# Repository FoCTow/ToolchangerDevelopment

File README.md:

# ToolchangerDevelopment
Overengineered 3D Printer Design

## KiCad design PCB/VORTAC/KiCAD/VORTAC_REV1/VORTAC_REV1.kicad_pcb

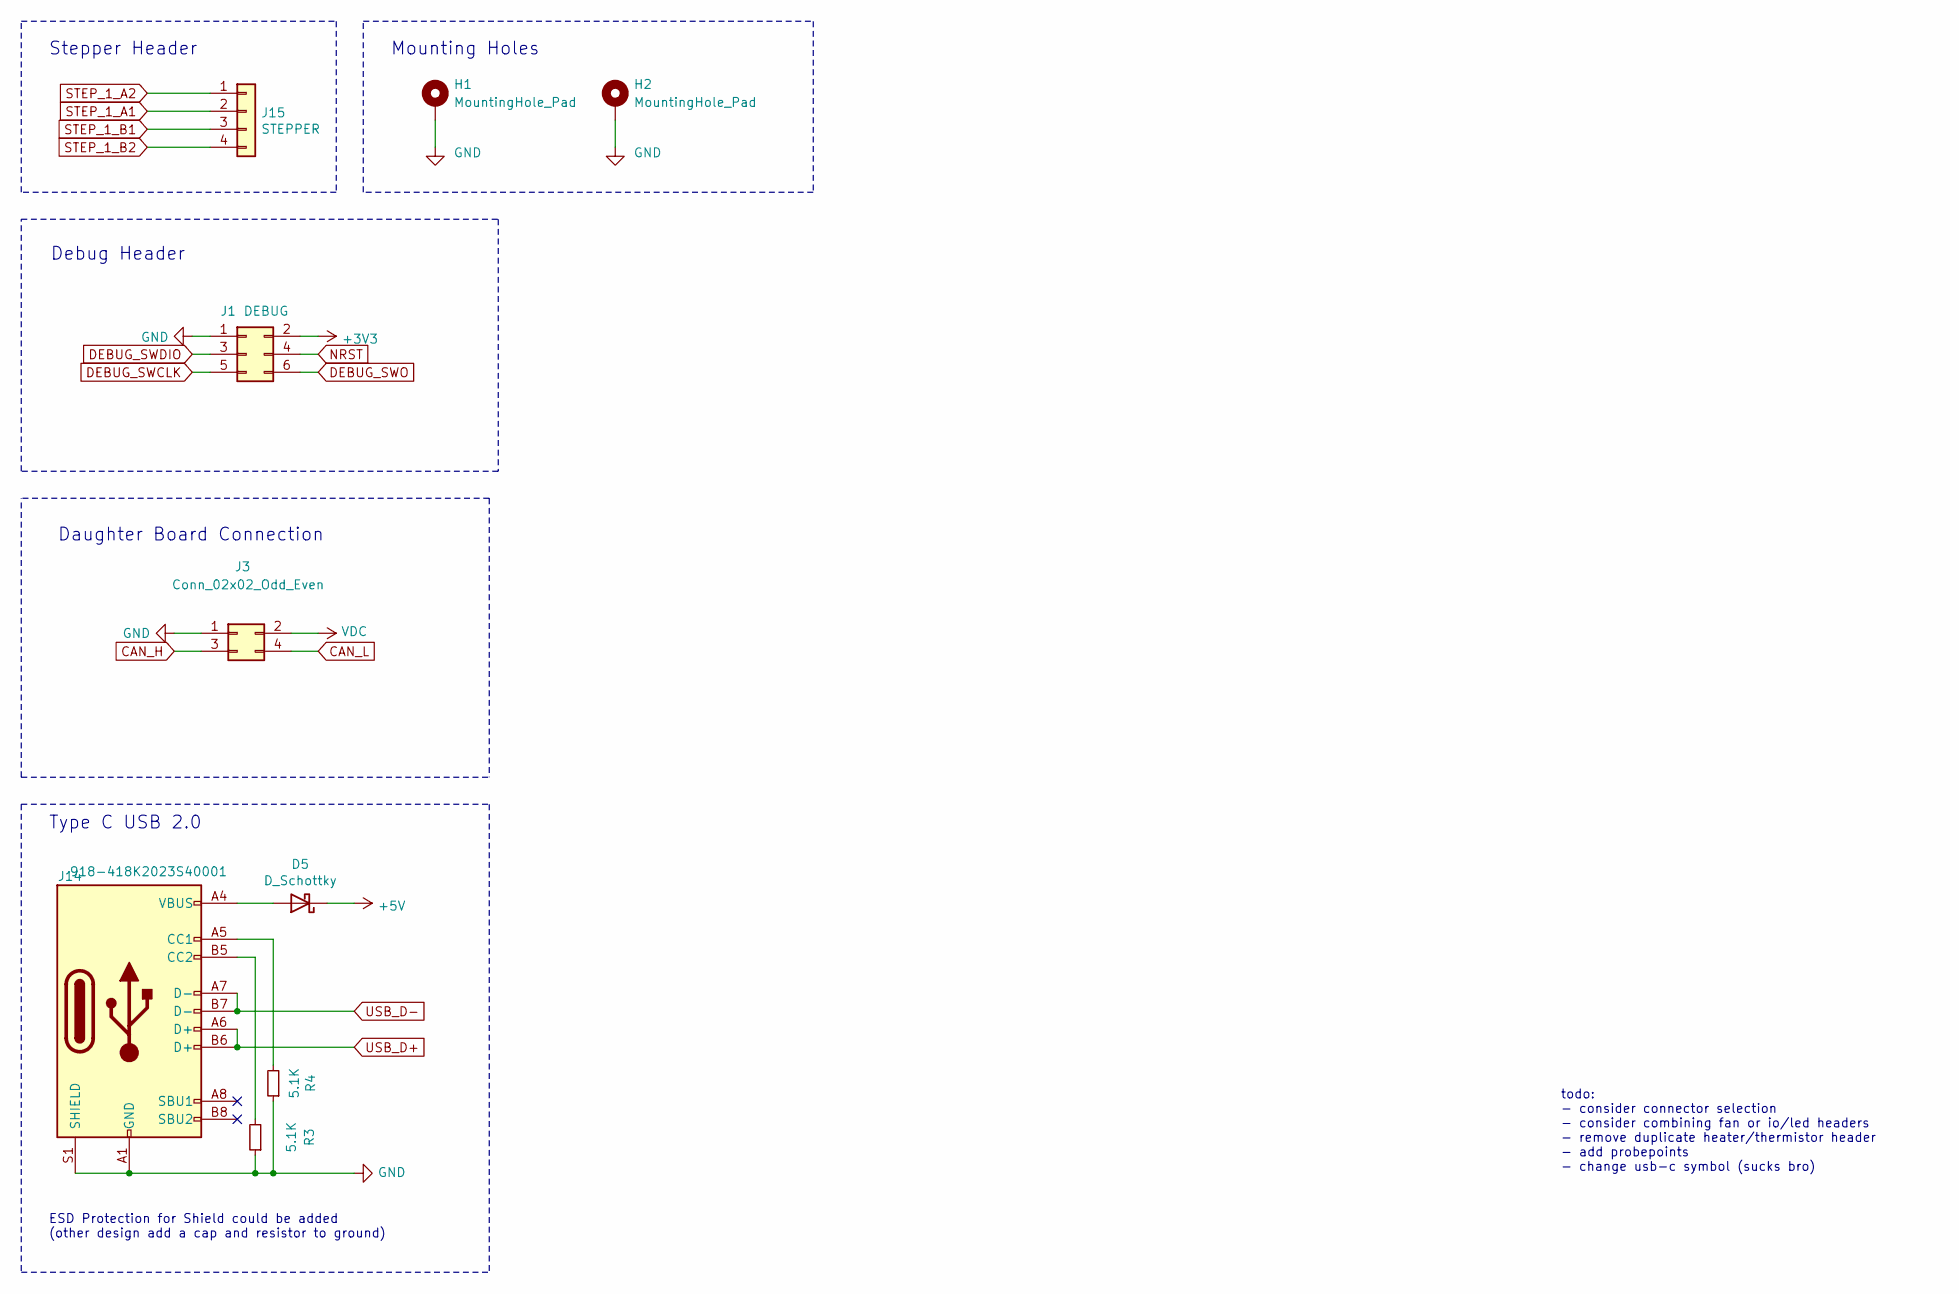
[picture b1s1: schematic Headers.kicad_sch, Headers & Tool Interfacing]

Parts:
D5: D_Schottky; D_SOD-323; LCSC C7420331
H1, H2: MountingHole_Pad; MountingHole_2.2mm_M2_Pad_Via_NTR
J1: DEBUG; PinSocket_2x03_P2.54mm_Vertical; LCSC C541853
J3: Conn_02x02_Odd_Even; PinHeader_2x02_P2.54mm_Vertical; LCSC C7501273
J14: 918-418K2023S40001; USB-C-SMD_TYPEC-303-ACP16; LCSC C720628
J15: STEPPER; Motor_Hand_Wire_pads
R3, R4: 5.1K; R_0402_1005Metric; LCSC C105872

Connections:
+3V3: J1.2; also elsewhere on the board
+5V: D5.1 (K); also elsewhere on the board
CAN_H: J3.3; also elsewhere on the board
CAN_L: J3.4; also elsewhere on the board
DEBUG_SWCLK: J1.5; also elsewhere on the board
DEBUG_SWDIO: J1.3; also elsewhere on the board
DEBUG_SWO: J1.6; also elsewhere on the board
GND: H1.1, H2.1, J1.1, J3.1, J14.A1 (GND), J14.A12 (GND), J14.B1 (GND), J14.B12 (GND), J14.S1 (SHIELD), R3.1, R4.1; also elsewhere on the board
NRST: J1.4; also elsewhere on the board
unnamed: D5.2 (A), J14.A4 (VBUS), J14.A9 (VBUS), J14.B4 (VBUS), J14.B9 (VBUS)
unnamed: J14.A5 (CC1), R4.2
unnamed: J14.B5 (CC2), R3.2
STEP_1_A1: J15.2; also elsewhere on the board
STEP_1_A2: J15.1; also elsewhere on the board
STEP_1_B1: J15.3; also elsewhere on the board
STEP_1_B2: J15.4; also elsewhere on the board
USB_D+: J14.A6 (D+), J14.B6 (D+); also elsewhere on the board
USB_D-: J14.A7 (D-), J14.B7 (D-); also elsewhere on the board
VDC: J3.2; also elsewhere on the board

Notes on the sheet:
todo: - consider connector selection - consider combining fan or io/led headers - remove duplicate heater/thermistor header - add probepoints - change usb-c symbol (sucks bro)
Daughter Board Connection
Stepper Header
Debug Header
Type C USB 2.0
ESD Protection for Shield could be added (other design add a cap and resistor to ground)
Mounting Holes

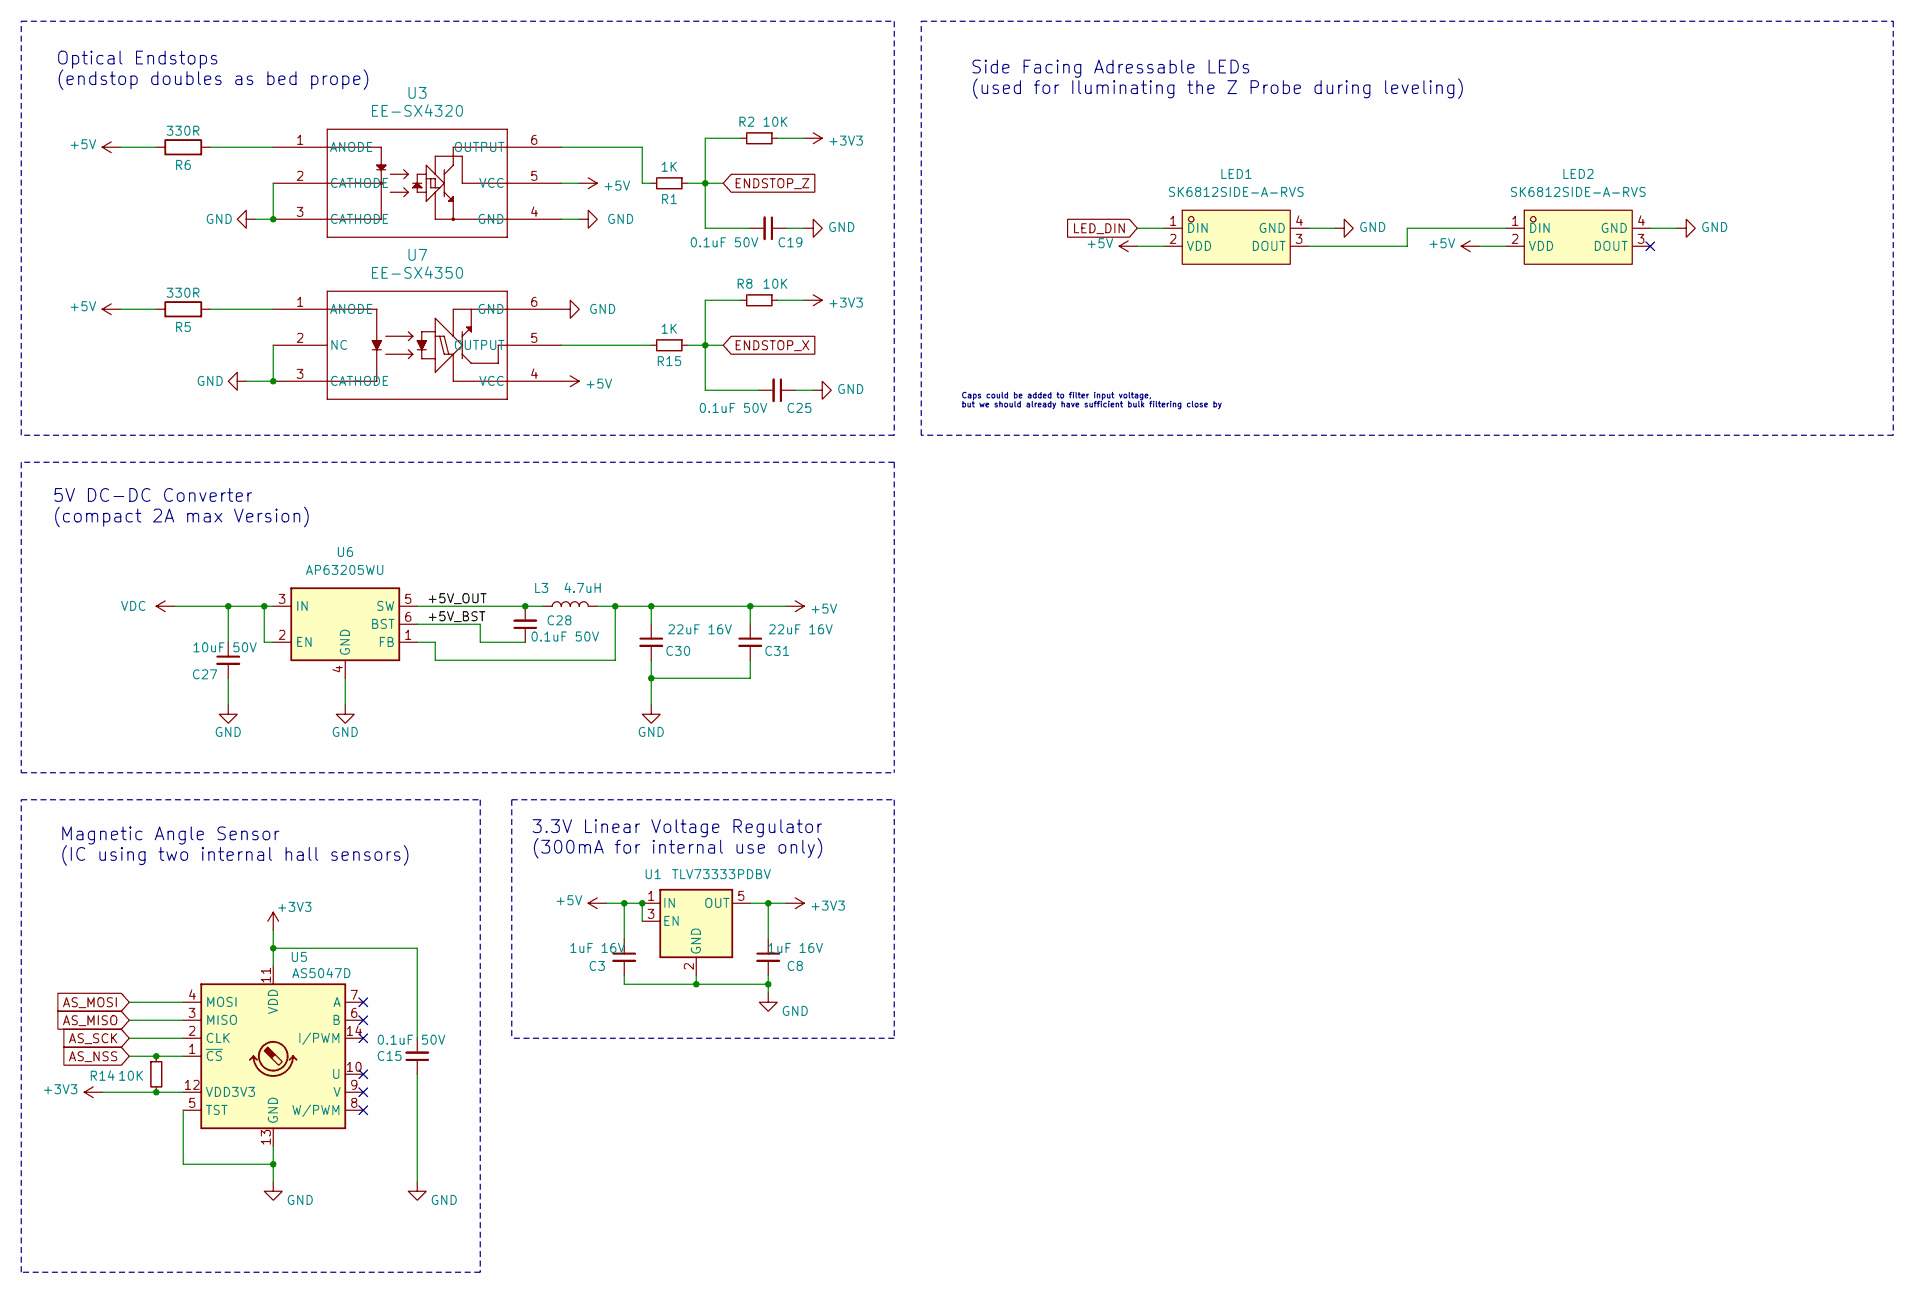
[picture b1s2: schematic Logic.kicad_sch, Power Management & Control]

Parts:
C3, C8: 1uF 16V; C_0603_1608Metric; LCSC C106248
C15, C19, C25, C28: 0.1uF 50V; C_0402_1005Metric; LCSC C5182432
C27: 10uF 50V; C_0805_2012Metric; LCSC C440198
C30, C31: 22uF 16V; C_0603_1608Metric; LCSC C2762594
L3: 4.7uH; IND-SMD_L4.0-W4.0_FNR40XXS; LCSC C167874
LED1, LED2: SK6812SIDE-A-RVS; LED-SMD_4P-L4.0-W1.6-L; LCSC C2890037
R1, R15: 1K; R_0402_1005Metric; LCSC C106235
R2, R8, R14: 10K; R_0402_1005Metric; LCSC C60490
R5, R6: 330R; R_0402_1005Metric; LCSC C6117577
U1: TLV73333PDBV; SOT-23-5; LCSC C408972
U3: EE-SX4320; SENSOR_EE-SX4320_OMR; LCSC C469129
U5: AS5047D; TSSOP-14_4.4x5mm_P0.65mm; LCSC C2693743
U6: AP63205WU; TSOT-23-6; LCSC C2071056
U7: EE-SX4350; SENSOR_EE-SX3350_OMR; LCSC C17524058

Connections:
+3V3: C8.1, C15.2, R2.1, R8.1, R14.2, U1.5 (OUT), U5.11 (VDD), U5.12 (VDD3V3); also elsewhere on the board
+5V: C3.1, C30.1, C31.1, L3.2, LED1.2 (VDD), LED2.2 (VDD), R5.1, R6.1, U1.1 (IN), U1.3 (EN), U3.5 (VCC), U6.1 (FB), U7.4 (VCC); also elsewhere on the board
/Logic/+5V_BST: C28.1, U6.6 (BST)
/Logic/+5V_OUT: C28.2, L3.1, U6.5 (SW)
AS_MISO: U5.3 (MISO); also elsewhere on the board
AS_MOSI: U5.4 (MOSI); also elsewhere on the board
AS_NSS: R14.1, U5.1 (~CS); also elsewhere on the board
AS_SCK: U5.2 (CLK); also elsewhere on the board
ENDSTOP_X: C25.2, R8.2, R15.1; also elsewhere on the board
ENDSTOP_Z: C19.2, R1.1, R2.2; also elsewhere on the board
GND: C3.2, C8.2, C15.1, C19.1, C25.1, C27.2, C30.2, C31.2, LED1.4 (GND), LED2.4 (GND), U1.2 (GND), U3.2 (CATHODE), U3.3 (CATHODE), U3.4 (GND), U5.5 (TST), U5.13 (GND), U6.4 (GND), U7.2 (NC), U7.3 (CATHODE), U7.6 (GND); also elsewhere on the board
LED_DIN: LED1.1 (DIN); also elsewhere on the board
unnamed: LED1.3 (DOUT), LED2.1 (DIN)
unnamed: R6.2, U3.1 (ANODE)
unnamed: R1.2, U3.6 (OUTPUT)
unnamed: R5.2, U7.1 (ANODE)
unnamed: R15.2, U7.5 (OUTPUT)
VDC: C27.1, U6.2 (EN), U6.3 (IN); also elsewhere on the board

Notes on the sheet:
Magnetic Angle Sensor (IC using two internal hall sensors)
Side Facing Adressable LEDs (used for Iluminating the Z Probe during leveling)
Optical Endstops (endstop doubles as bed prope)
3.3V Linear Voltage Regulator (300mA for internal use only)
Caps could be added to filter input voltage, but we should already have sufficient bulk filtering close by
5V DC-DC Converter (compact 2A max Version)

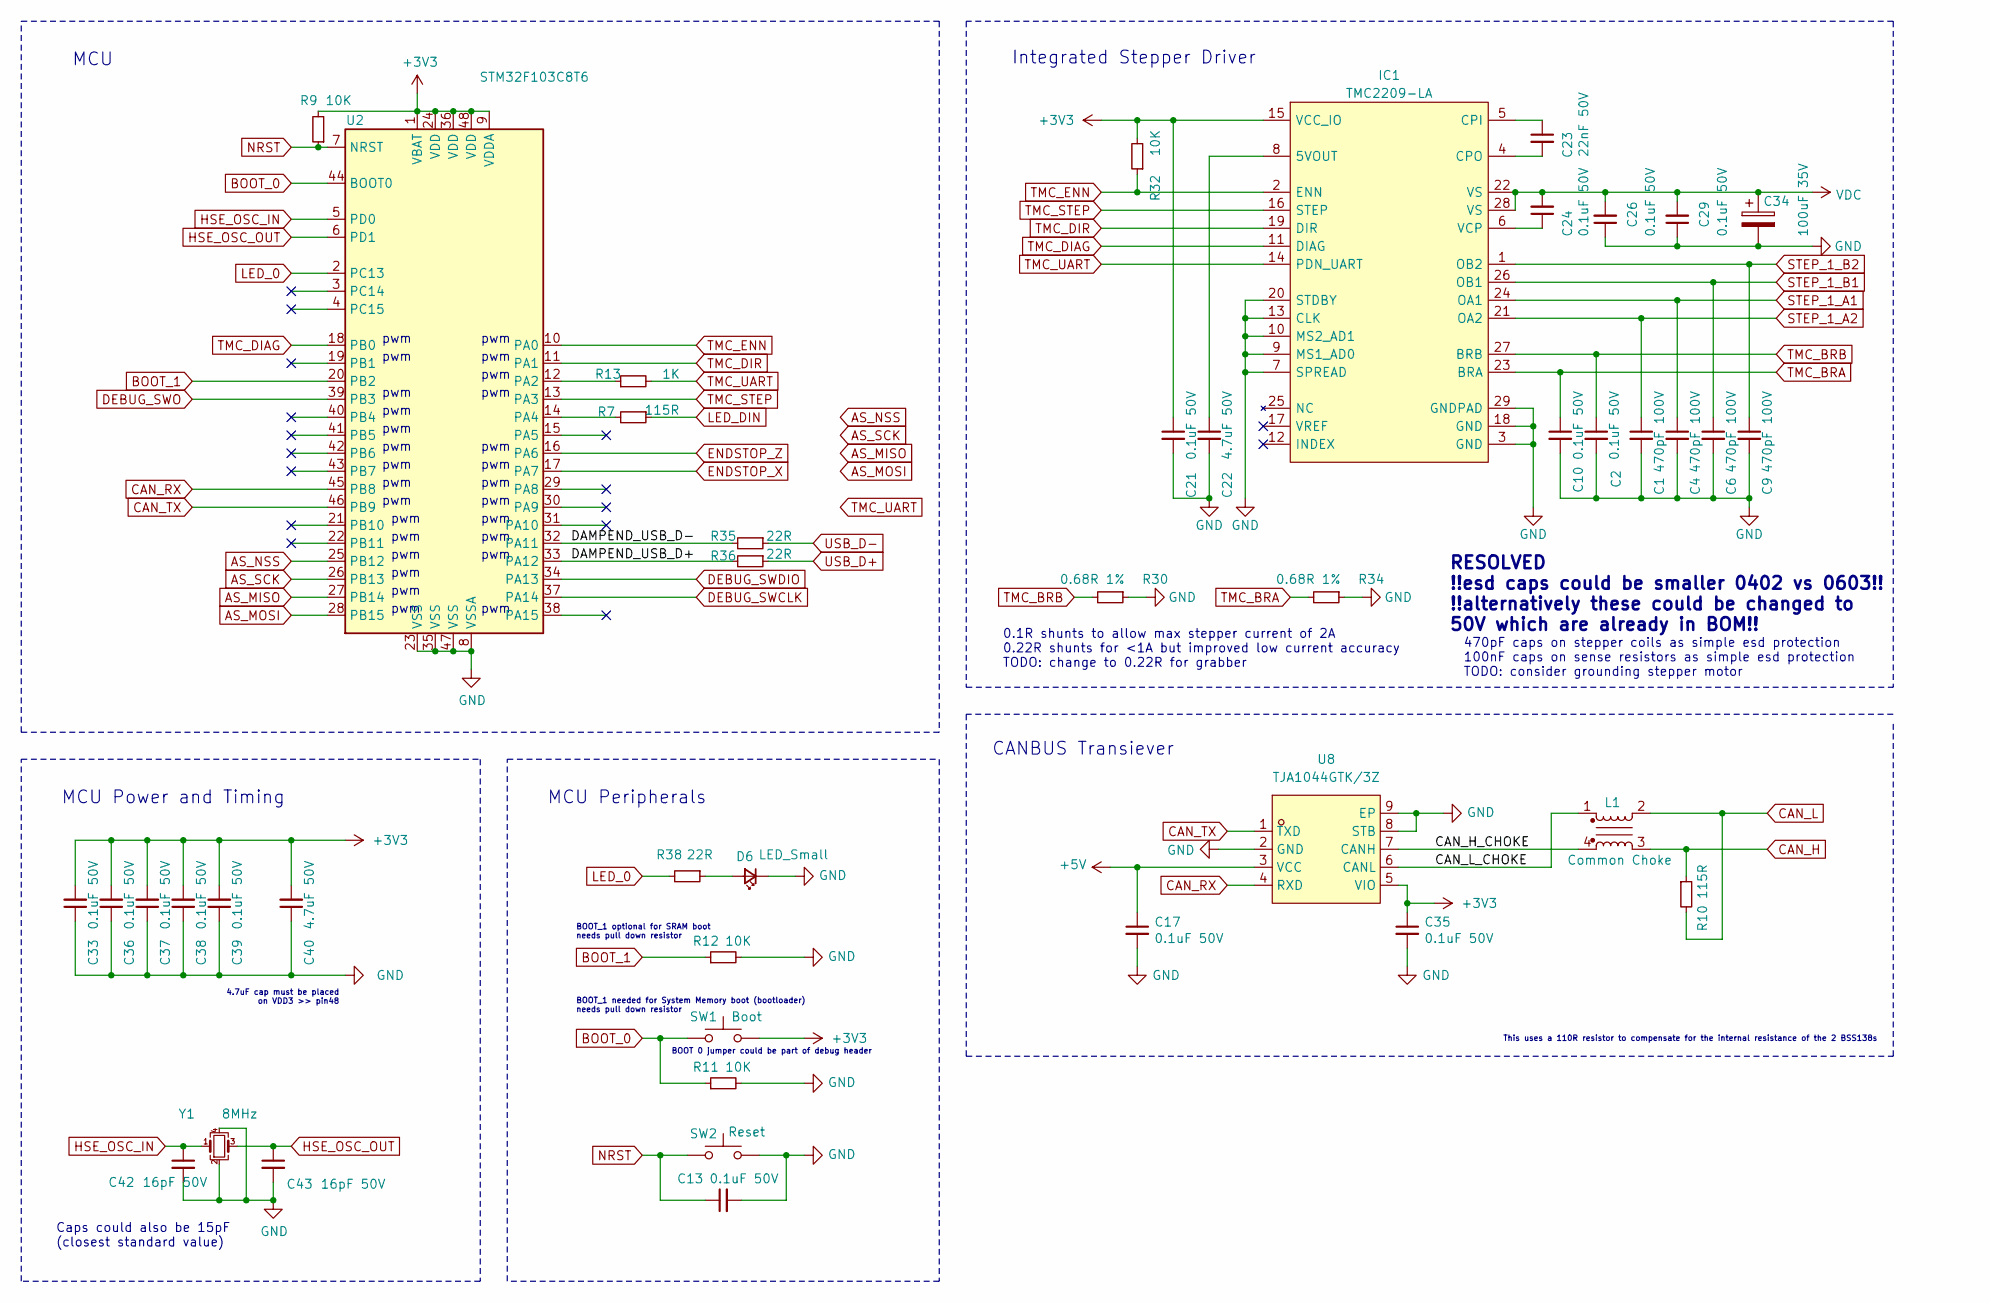
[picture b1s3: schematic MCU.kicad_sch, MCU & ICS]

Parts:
C1, C4, C6, C9: 470pF 100V; C_0603_1608Metric; LCSC C326973
C2, C10, C13, C17, C21, C24, C26, C29, C33, C35, C36, C37, C38, C39: 0.1uF 50V; C_0402_1005Metric; LCSC C5182432
C22, C40: 4.7uF 50V; C_0603_1608Metric; LCSC C513577
C23: 22nF 50V; C_0402_1005Metric; LCSC C107026
C34: 100uF 35V; CP_Elec_6.3x7.7; LCSC C2983388
C42, C43: 16pF 50V; C_0402_1005Metric; LCSC C513591
D6: LED_Small; LED_0402_1005Metric; LCSC C130724
IC1: TMC2209-LA; tmc_2209_package; LCSC C2150710
L1: Common Choke; L_CommonModeChoke_Coilcraft_0805USB; LCSC C3029267
R7, R10: 115R; R_0402_1005Metric; LCSC C295872
R9, R11, R12, R32: 10K; R_0402_1005Metric; LCSC C60490
R13: 1K; R_0402_1005Metric; LCSC C106235
R30, R34: 0.68R 1%; R_0805_2012Metric; LCSC C912570
R35, R36, R38: 22R; R_0402_1005Metric; LCSC C6117700
SW1: Boot; KEY-SMD_B3U-1000PM; LCSC C231329
SW2: Reset; KEY-SMD_B3U-1000PM; LCSC C231329
U2: STM32F103C8T6; LQFP-48_7x7mm_P0.5mm; LCSC C8734
U8: TJA1044GTK/3Z; HVSON-8-1EP_3x3mm_P0.65mm_EP1.6x2.4mm; LCSC C2157795
Y1: 8MHz; Crystal_SMD_3225-4Pin_3.2x2.5mm; LCSC C5261255

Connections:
+3V3: C21.1, C33.2, C35.1, C36.2, C37.2, C38.2, C39.2, C40.2, IC1.15 (VCC_IO), R9.2, R32.2, SW1.2, U2.1 (VBAT), U2.9 (VDDA), U2.24 (VDD), U2.36 (VDD), U2.48 (VDD), U8.5 (VIO); also elsewhere on the board
+5V: C17.1, U8.3 (VCC); also elsewhere on the board
/MCU/CAN_H_CHOKE: L1.4, U8.7 (CANH)
/MCU/CAN_L_CHOKE: L1.1, U8.6 (CANL)
/MCU/DAMPEND_USB_D+: R36.2, U2.33 (PA12)
/MCU/DAMPEND_USB_D-: R35.2, U2.32 (PA11)
AS_MISO: U2.27 (PB14); also elsewhere on the board
AS_MOSI: U2.28 (PB15); also elsewhere on the board
AS_NSS: U2.25 (PB12); also elsewhere on the board
AS_SCK: U2.26 (PB13); also elsewhere on the board
BOOT_0: R11.1, SW1.1, U2.44 (BOOT0)
BOOT_1: R12.1, U2.20 (PB2)
CAN_H: L1.3, R10.1; also elsewhere on the board
CAN_L: L1.2, R10.2; also elsewhere on the board
CAN_RX: U2.45 (PB8), U8.4 (RXD)
CAN_TX: U2.46 (PB9), U8.1 (TXD)
DEBUG_SWCLK: U2.37 (PA14); also elsewhere on the board
DEBUG_SWDIO: U2.34 (PA13); also elsewhere on the board
DEBUG_SWO: U2.39 (PB3); also elsewhere on the board
ENDSTOP_X: U2.17 (PA7); also elsewhere on the board
ENDSTOP_Z: U2.16 (PA6); also elsewhere on the board
GND: C1.2, C2.2, C4.2, C6.2, C9.2, C10.2, C13.2, C17.2, C21.2, C22.2, C26.1, C29.1, C33.1, C34.2, C35.2, C36.1, C37.1, C38.1, C39.1, C40.1, C42.2, C43.2, D6.1 (K), IC1.3 (GND), IC1.7 (SPREAD), IC1.9 (MS1_AD0), IC1.10 (MS2_AD1), IC1.13 (CLK), IC1.18 (GND), IC1.20 (STDBY), IC1.29 (GNDPAD), R11.2, R12.2, R30.1, R34.1, SW2.2, U2.8 (VSSA), U2.23 (VSS), U2.35 (VSS), U2.47 (VSS), U8.2 (GND), U8.8 (STB), U8.9 (EP), Y1.2, Y1.4; also elsewhere on the board
HSE_OSC_IN: C42.1, U2.5 (PD0), Y1.1
HSE_OSC_OUT: C43.1, U2.6 (PD1), Y1.3
LED_0: R38.2, U2.2 (PC13)
LED_DIN: R7.1; also elsewhere on the board
NRST: C13.1, R9.1, SW2.1, U2.7 (NRST); also elsewhere on the board
unnamed: D6.2 (A), R38.1
unnamed: C22.1, IC1.8 (5VOUT)
unnamed: C23.1, IC1.5 (CPI)
unnamed: C23.2, IC1.4 (CPO)
unnamed: C24.1, IC1.6 (VCP)
unnamed: R13.1, U2.12 (PA2)
unnamed: R7.2, U2.14 (PA4)
STEP_1_A1: C4.1, IC1.24 (OA1); also elsewhere on the board
STEP_1_A2: C1.1, IC1.21 (OA2); also elsewhere on the board
STEP_1_B1: C6.1, IC1.26 (OB1); also elsewhere on the board
STEP_1_B2: C9.1, IC1.1 (OB2); also elsewhere on the board
TMC_BRA: C10.1, IC1.23 (BRA), R34.2
TMC_BRB: C2.1, IC1.27 (BRB), R30.2
TMC_DIAG: IC1.11 (DIAG), U2.18 (PB0)
TMC_DIR: IC1.19 (DIR), U2.11 (PA1)
TMC_ENN: IC1.2 (ENN), R32.1, U2.10 (PA0)
TMC_STEP: IC1.16 (STEP), U2.13 (PA3)
TMC_UART: IC1.14 (PDN_UART), R13.2
USB_D+: R36.1; also elsewhere on the board
USB_D-: R35.1; also elsewhere on the board
VDC: C24.2, C26.2, C29.2, C34.1, IC1.22 (VS), IC1.28 (VS); also elsewhere on the board

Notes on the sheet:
pwm
RESOLVED !!esd caps could be smaller 0402 vs 0603!! !!alternatively these could be changed to 50V which are already in BOM!!
0.1R shunts to allow max stepper current of 2A 0.22R shunts for <1A but improved low current accuracy TODO: change to 0.22R for grabber
Caps could also be 15pF (closest standard value)
BOOT_1 optional for SRAM boot needs pull down resistor
MCU Power and Timing
This uses a 110R resistor to compensate for the internal resistance of the 2 BSS138s
Integrated Stepper Driver
4.7uF cap must be placed on VDD3 >> pin48
470pF caps on stepper coils as simple esd protection 100nF caps on sense resistors as simple esd protection TODO: consider grounding stepper motor
BOOT 0 jumper could be part of debug header
MCU Peripherals
BOOT_1 needed for System Memory boot (bootloader) needs pull down resistor
CANBUS Transiever
MCU

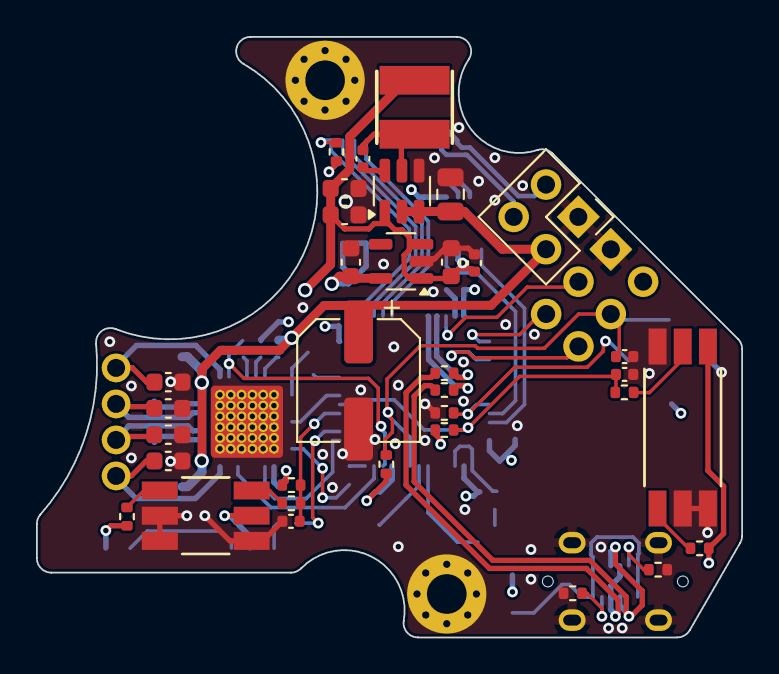
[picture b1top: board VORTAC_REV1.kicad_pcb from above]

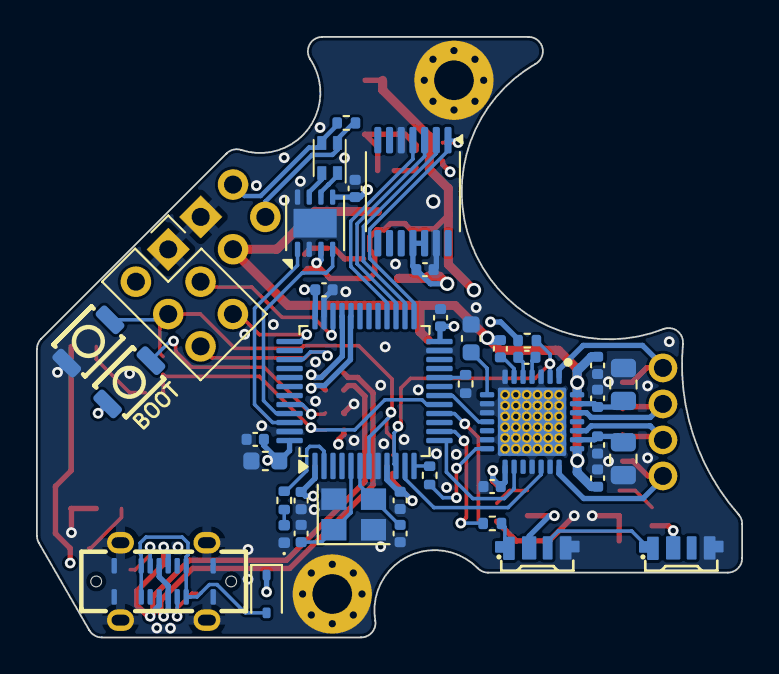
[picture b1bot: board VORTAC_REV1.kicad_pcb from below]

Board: 4 copper layers, 39.2 x 33.4 mm, 77 parts (40 on the bottom side), 58 nets.

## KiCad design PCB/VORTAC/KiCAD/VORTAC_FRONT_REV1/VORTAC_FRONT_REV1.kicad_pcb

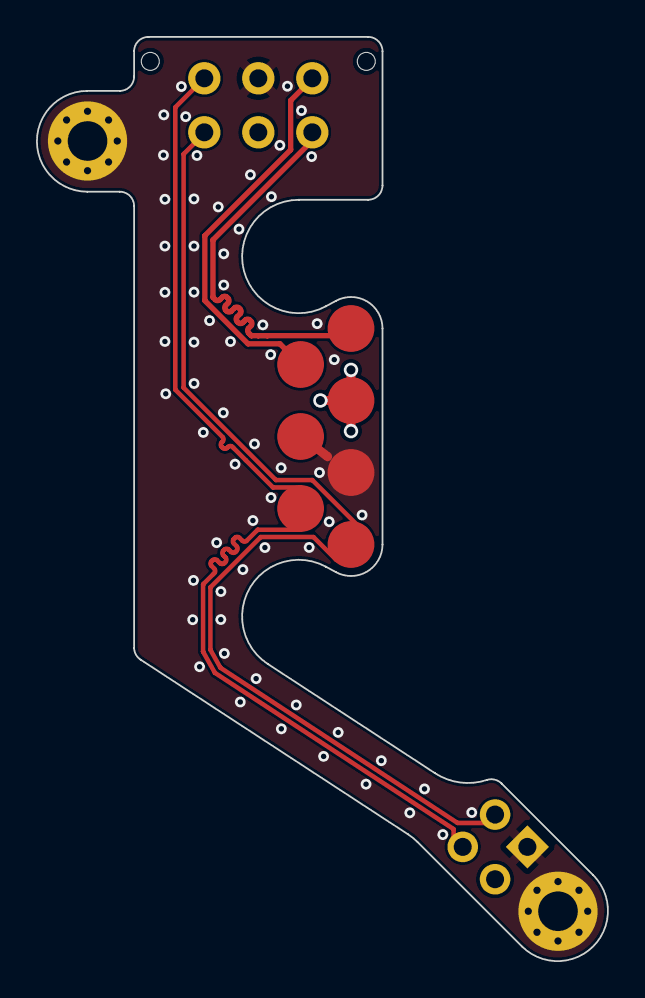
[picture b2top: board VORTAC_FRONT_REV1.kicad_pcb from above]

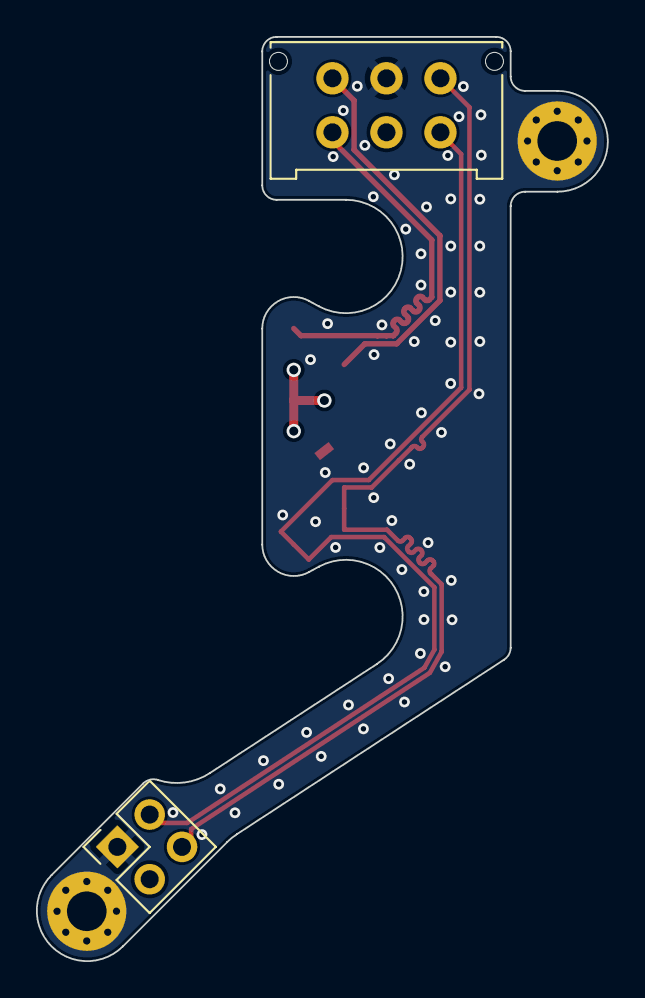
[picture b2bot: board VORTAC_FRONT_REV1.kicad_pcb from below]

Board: 4 copper layers, 31.7 x 51.3 mm, 6 parts (2 on the bottom side), 7 nets.

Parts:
H1, H2: MountingHole_Pad; MountingHole_2.2mm_M2_Pad_Via_NTR
J1: Conn_02x02_Odd_Even; PinSocket_2x02_P2.54mm_Vertical
J2: Conn_02x03_Odd_Even; Molex_Micro-Fit_3.0_43045-0612_2x03_P3.00mm_Vertical
J3: Conn_01x07; mill-max-0881-1-15-20-82-14-11-0_LandingPads_Simple
NT1: NetTie_2; NetTie-2_SMD_Pad0.5mm

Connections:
CAN_H: J1.3, J2.1, J3.7
CAN_L: J1.4, J2.4, J3.6
GND: H1.1, H2.1, J1.1, J2.5, J3.5, NT1.2
TOOL_ID: J3.4, NT1.1
USB_D+: J2.3, J3.1
USB_D-: J2.6, J3.2
VDC: J1.2, J2.2, J3.3

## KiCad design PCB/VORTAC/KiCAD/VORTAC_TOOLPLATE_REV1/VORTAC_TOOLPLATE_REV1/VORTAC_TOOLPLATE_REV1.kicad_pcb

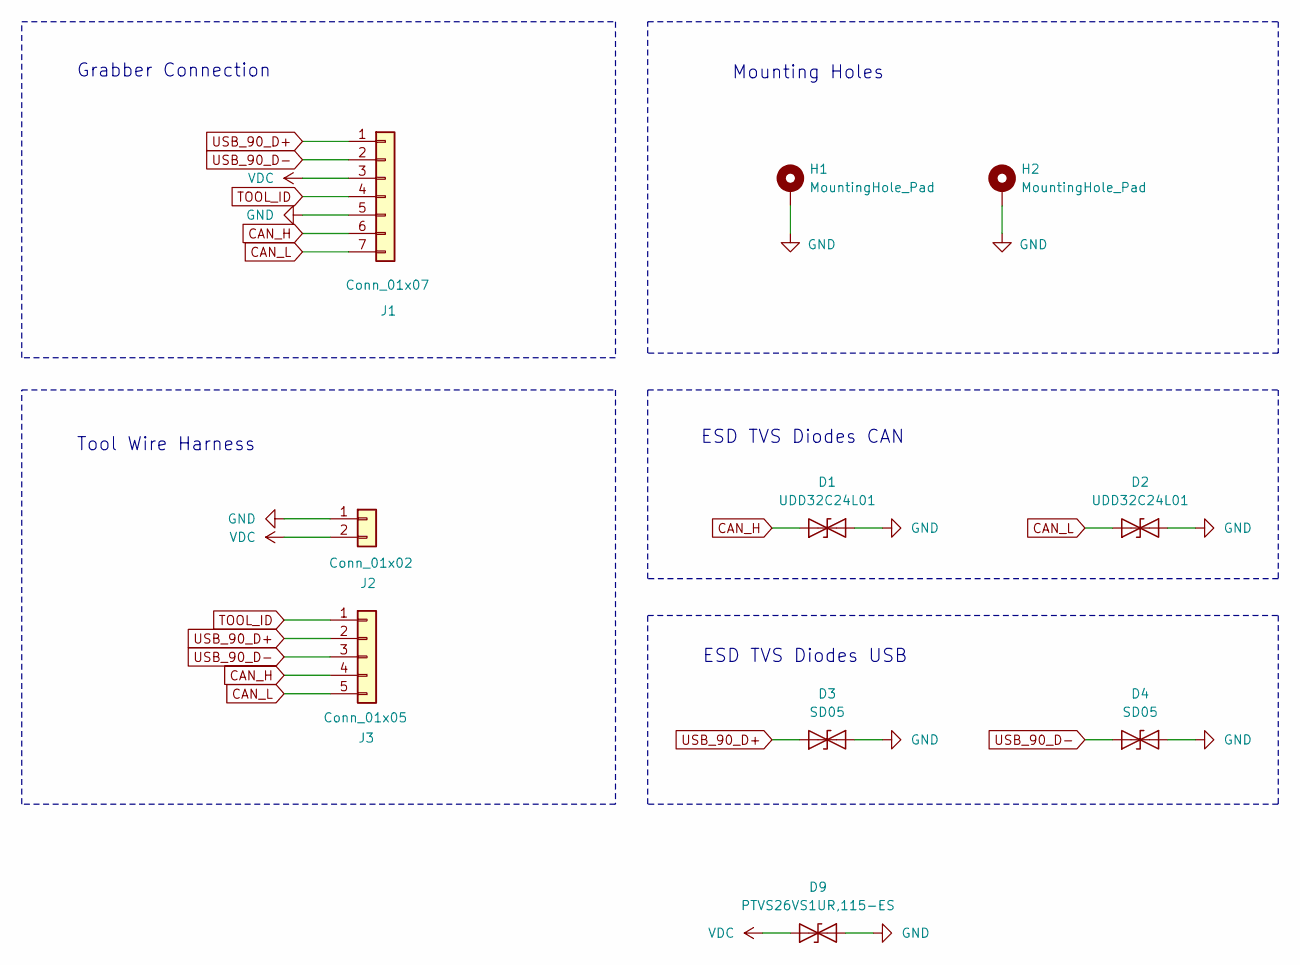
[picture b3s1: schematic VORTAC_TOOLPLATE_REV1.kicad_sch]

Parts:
D1, D2: UDD32C24L01; D_SOD-323; LCSC C19188728
D3, D4: SD05; D_SOD-323; LCSC C502527
D9: PTVS26VS1UR,115-ES; D_SOD-123F; LCSC C41409305
H1, H2: MountingHole_Pad; MountingHole_2.2mm_M2_Pad_Via_NTR
J1: Conn_01x07; mill-max-0881-1-15-20-82-14-11-0_LandingPads_ContactPad_PTH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
J2: Conn_01x02; Toolplate_Solderpoint_01x02_Power
J3: Conn_01x05; Toolplate_Solderpoint_01x05_Data

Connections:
CAN_H: D1.2 (A2), J1.6, J3.4
CAN_L: D2.2 (A2), J1.7, J3.5
GND: D1.1 (A1), D2.1 (A1), D3.1 (A1), D4.1 (A1), D9.1 (A1), H1.1, H2.1, J1.5, J2.1
TOOL_ID: J1.4, J3.1
USB_90_D+: D3.2 (A2), J1.1, J3.2
USB_90_D-: D4.2 (A2), J1.2, J3.3
VDC: D9.2 (A2), J1.3, J2.2

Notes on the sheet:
Grabber Connection
Tool Wire Harness
ESD TVS Diodes CAN
ESD TVS Diodes USB
Mounting Holes

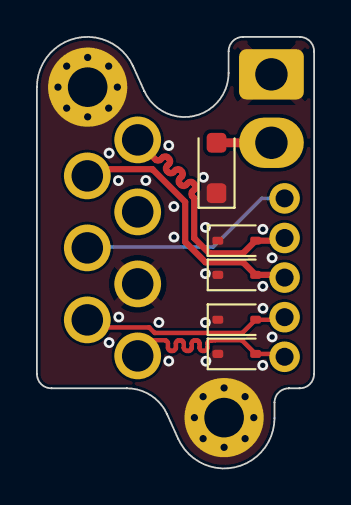
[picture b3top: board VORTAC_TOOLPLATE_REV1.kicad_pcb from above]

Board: 4 copper layers, 15.4 x 24.0 mm, 10 parts (0 on the bottom side), 7 nets.

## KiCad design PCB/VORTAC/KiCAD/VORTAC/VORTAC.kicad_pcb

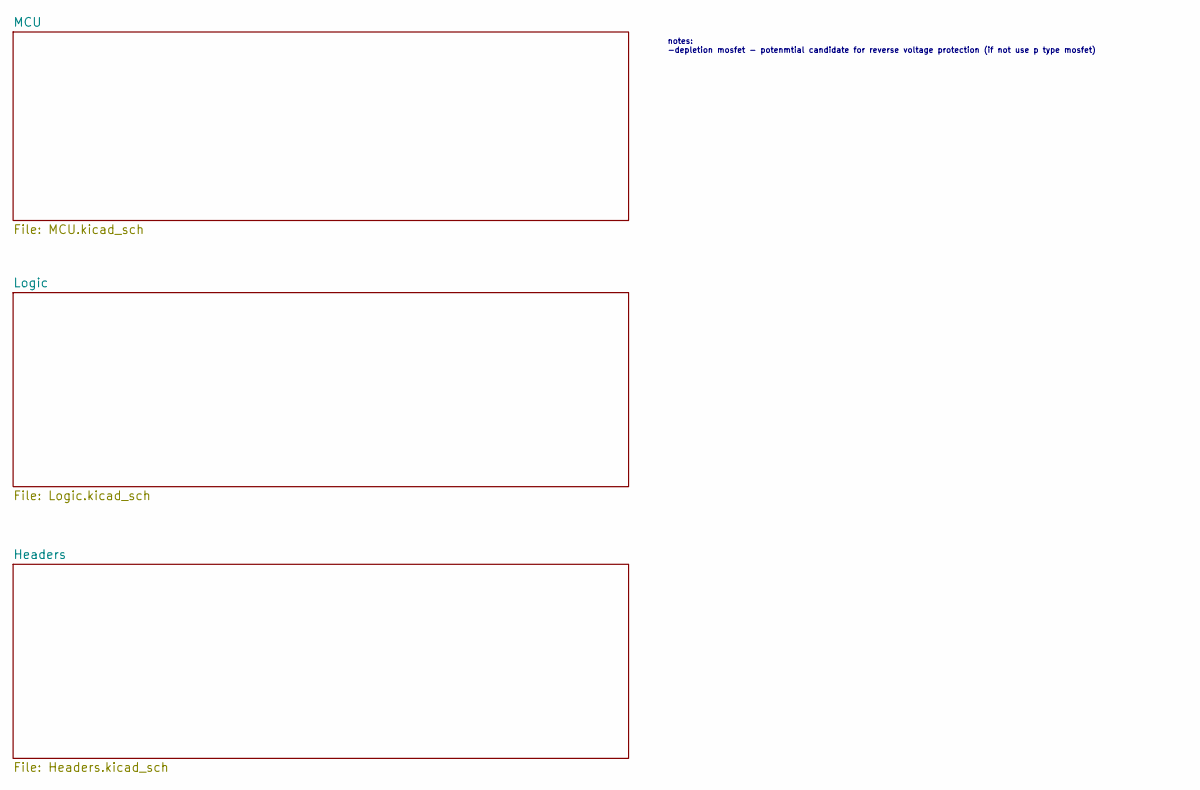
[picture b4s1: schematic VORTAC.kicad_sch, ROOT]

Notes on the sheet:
notes: -depletion mosfet - potenmtial candidate for reverse voltage protection (if not use p type mosfet)
